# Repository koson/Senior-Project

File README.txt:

This is the repository for the "Granny Safe" senior project

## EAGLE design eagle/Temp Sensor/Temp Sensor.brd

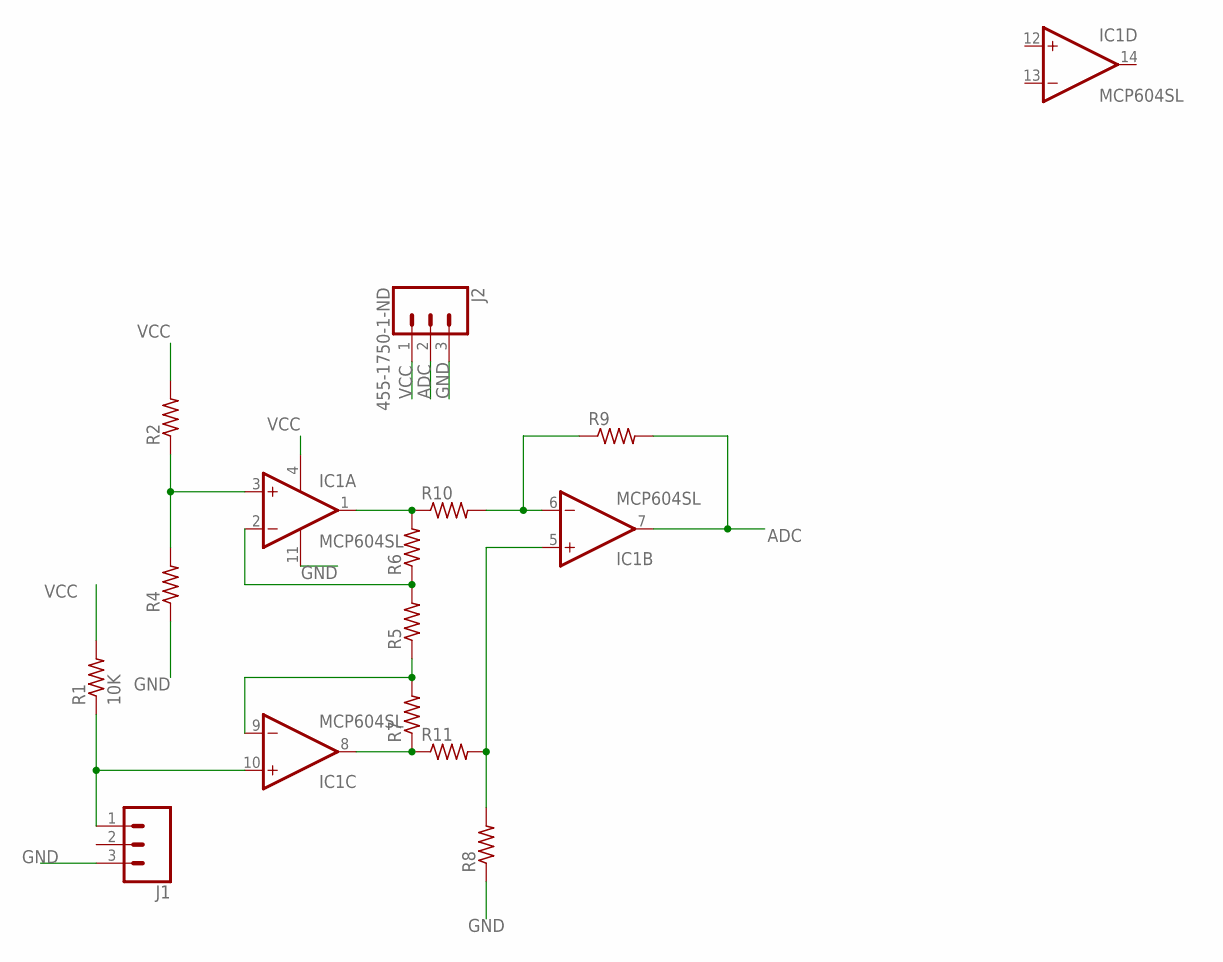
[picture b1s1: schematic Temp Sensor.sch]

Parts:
IC1: MCP604SL; SO14
J1: CONN_03SCREW_LOCK; SCREWTERMINAL-3.5MM-3_LOCK.007S
J2: 455-1750-1-ND; 1X03
R1: 10K; R0603
R2, R4, R5, R6, R7, R8, R9, R10, R11: R-US_R0603; R0603

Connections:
ADC: IC1.7 (OUT), J2.2, R9.2
GND: IC1.11 (V-), J1.3, J2.3, R4.1, R8.1
unnamed: IC1.10 (+IN), J1.1, R1.1
unnamed: IC1.3 (+IN), R2.1, R4.2
unnamed: IC1.8 (OUT), R7.1, R11.1
unnamed: IC1.1 (OUT), R6.2, R10.1
unnamed: IC1.2 (-IN), R5.2, R6.1
unnamed: IC1.9 (-IN), R5.1, R7.2
unnamed: IC1.5 (+IN), R8.2, R11.2
unnamed: IC1.6 (-IN), R9.1, R10.2
VCC: IC1.4 (V+), J2.1, R1.2, R2.2

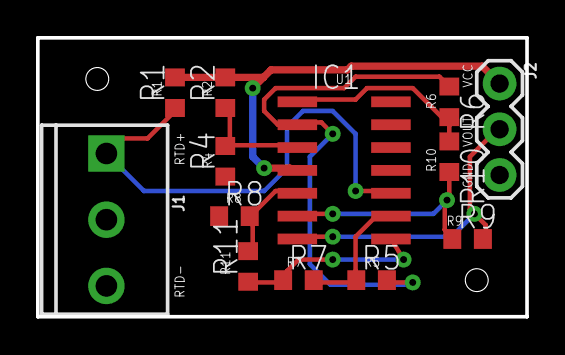
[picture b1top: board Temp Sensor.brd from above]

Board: 2 copper layers, 27.2 x 15.5 mm, 13 parts (0 on the bottom side), 11 nets.

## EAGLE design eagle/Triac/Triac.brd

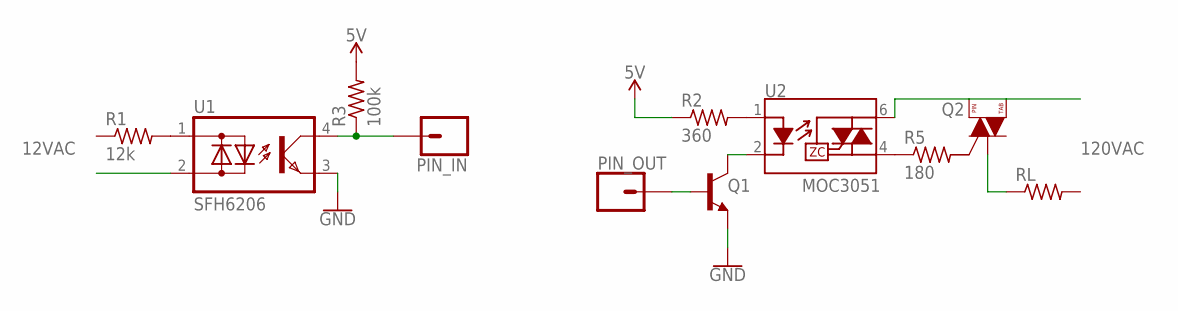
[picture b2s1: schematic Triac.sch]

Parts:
PIN_IN: CONN_01; 1X01
PIN_OUT: CONN_01; 1X01
Q1: TRANS_NPN-MMBTA42; SOT23-3
Q2: BT137-600E; SOT223
R1: 12k; R0603
R2: 360; R0603
R3: 100k; R0603
R5: 180; R0603
RL: R-US_R0603; R0603
U1: SFH6206; DIL4-SMD
U2: TRIAC_OPTOCOUPLER-MOC3063SM; DIP8SMD

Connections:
5V: R2.1, R3.2
GND: Q1.2 (E), U1.3 (E)
unnamed: R1.2, U1.1 (AC1)
unnamed: PIN_IN.1, R3.1, U1.4 (C)
unnamed: R2.2, U2.1 (A)
unnamed: R5.1, U2.4 (T2)
unnamed: Q2.2 (T2), Q2.4 (T2), U2.6 (T1)
unnamed: Q1.3 (C), U2.2 (K)
unnamed: PIN_OUT.1, Q1.1 (B)
unnamed: Q2.1 (T1), RL.1

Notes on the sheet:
MOC3051
12VAC
120VAC

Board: 2 copper layers, 11 parts (0 on the bottom side), 10 nets, no tracks yet.

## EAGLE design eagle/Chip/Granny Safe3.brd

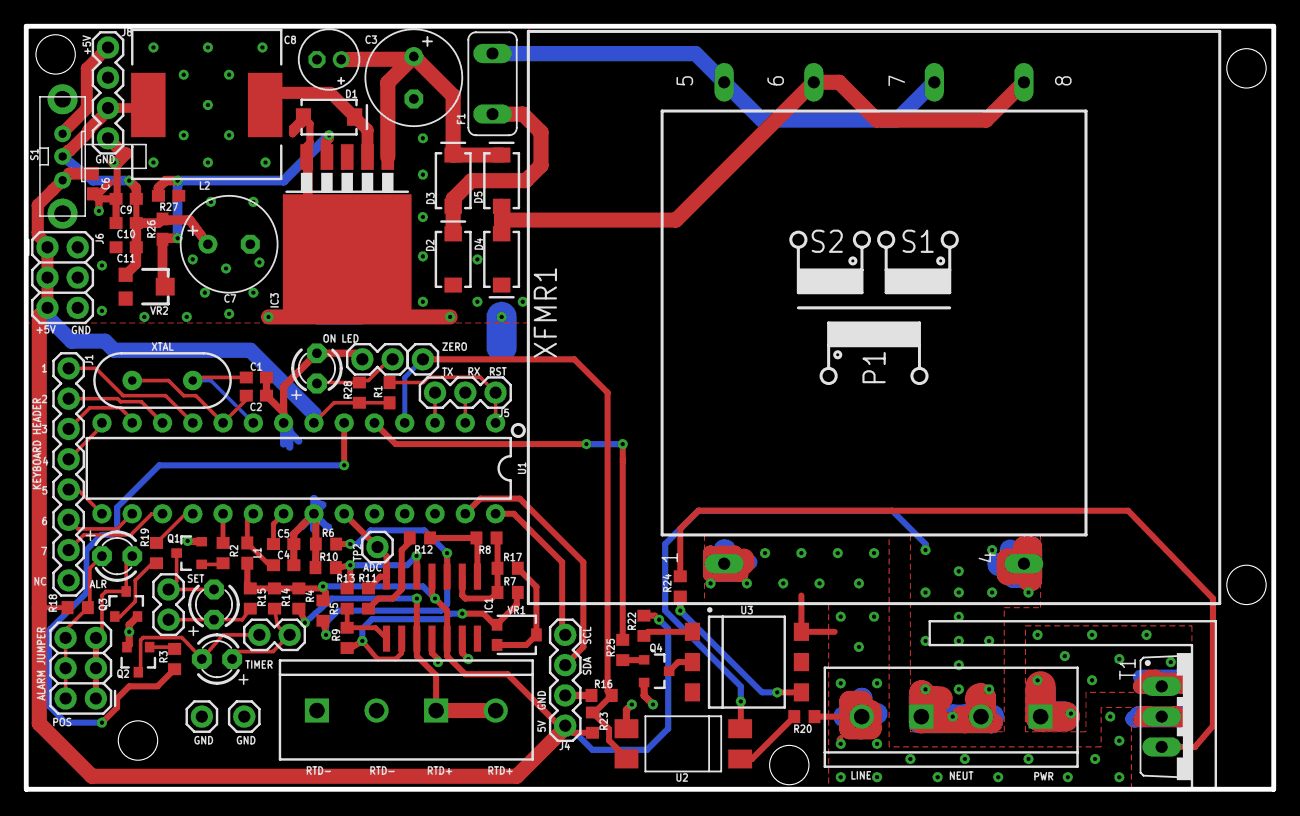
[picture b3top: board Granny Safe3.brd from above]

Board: 2 copper layers, 104.6 x 64.0 mm, 85 parts (0 on the bottom side), 60 nets.

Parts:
ALR_LED: LED3MM
C1, C2: 22pF; 0603
C3, C7: 470u; E3,5-8
C4, C5, C6, C9: 0.1uF; 0603
C8: 100u; E2-5
C10: 100pF; 0603
C11: 1nF; 0603
D1, D2, D3, D4, D5: SMA-DIODE
F1: 1.5A; TE5
H1, H2, H3, H4, H5: STAND-OFF
IC1: MCP604SL; SO14
IC3: TO263-5
J1: 3x4 Keypad; 1X08
J2, J6: FEMALE 2x3; 2X3
J3, J10: SCREW-4; SCREWTERMINAL-5MM-2
J4: i2c_16x2; 1X04
J5: 1X03
J7, J11, J12: 1X02
J8: RES JUMPER; 1X04
L1: 10uH; 0603
L2: INDUCTOR; CR75
ON_LED: LED3MM
Q1, Q2, Q3: SOT23-3
Q4: 2N3904; SOT23-3
R1: 10k; 0603
R2, R3, R19, R25: 2k; R0603
R4, R5: 2.4k; R0603
R6: 100; R0603
R7, R20, R23: 10k; R0603
R8, R9: 20k; R0603
R10, R11: 15k; R0603
R12, R13: 3k; R0603
R14, R15, R18, R28: 150; R0603
R16: 1M; R0603
R17: 5k; R0603
R22: 220; R0603
R24: 180; R0603
R26: 3.3k; 0603
R27: 1k; 0603
S1: EG1213
SET_LED: LED3MM
T1: BT137; TO220BV
TIM_LED: LED3MM
TP1, TP2, TP3, TP5: 1X01
U1: 328P; DIP28
U2: SFH6206; DIL4-SMD
U3: MOC3051; DIP8SMD
VR1: 10k; TRIMPOT-SMD-3MM-CLOSED
VR2: 10k; TRIMPOT-SMD-TC33X
XFMR1: EE20-2
XTAL: 16MHz; HC49US

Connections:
5V: C6.1, IC1.4, IC1.12, J4.1, J6.1, J6.3, J6.5, L1.1, R1.2, R4.2, R5.2, R14.2, R15.2, R18.2, R22.1, R23.2, R28.2, S1.1, U1.7
ADC0: IC1.7, R11.2, TP2.1, U1.23
ALR: R19.1, U1.18
GATE: R25.1, U1.5
GND: C1.1, C2.1, C3.-, C4.2, C5.2, C6.2, C7.-, C8.-, C9.2, C10.2, C11.2, D1.A, D2.A, D4.C, IC1.11, IC1.13, IC3.3, IC3.5, IC3.6, J3.1, J3.2, J4.2, J6.2, J6.4, J6.6, J8.4, J12.2, ON_LED.K, Q1.2, Q2.2, Q3.2, Q4.2, R6.1, R10.1, R16.1, R27.1, TP3.1, TP5.1, U1.8, U1.22, U2.3, VR2.3
LINE: J10.4, R20.1, T1.T2, U3.6, XFMR1.1
unnamed: C1.2, U1.9, XTAL.2
unnamed: C2.2, U1.10, XTAL.1
unnamed: J1.7, U1.17
unnamed: J8.1, S1.3
unnamed: C5.1, U1.21
unnamed: J1.6, U1.16
unnamed: J1.5, U1.15
unnamed: J1.4, U1.14
unnamed: J1.3, U1.13
unnamed: J1.2, U1.12
unnamed: J1.1, U1.11
unnamed: Q1.1, R2.2
unnamed: IC1.10, J3.3, J3.4, R4.1
unnamed: Q2.1, R3.2
unnamed: IC1.3, R5.1, R6.2
unnamed: IC1.1, R8.2, R12.1
unnamed: J7.1, R15.1, SET_LED.A
unnamed: J11.1, R14.1, TIM_LED.A
unnamed: J11.2, Q2.3, TIM_LED.K
unnamed: J7.2, Q1.3, SET_LED.K
unnamed: R17.2, VR1.2, VR1.3
unnamed: D2.C, D3.A, F1.2
unnamed: ALR_LED.K, J2.1, J2.3, J2.5, Q3.3
unnamed: IC1.2, R7.2, R8.1, R17.1
unnamed: IC1.8, R9.1, R13.1
unnamed: IC1.9, R7.1, R9.2, VR1.1
unnamed: IC1.5, R10.2, R13.2
unnamed: IC1.6, R11.1, R12.2
unnamed: R20.2, U2.1
unnamed: R24.2, T1.G
unnamed: R22.2, U3.1
unnamed: R24.1, U3.4
unnamed: IC3.4, R26.1, R27.2, VR2.2
unnamed: Q4.3, U3.2
unnamed: Q4.1, R25.2
unnamed: J12.1, ON_LED.A, R28.1
unnamed: F1.1, XFMR1.5, XFMR1.7
unnamed: C7.+, C9.1, C10.1, C11.1, J8.3, L2.P$2, R26.2, S1.2, VR2.1
unnamed: ALR_LED.A, J2.2, J2.4, J2.6, R18.1
unnamed: Q3.1, R19.2
unnamed: D4.A, D5.A, XFMR1.6, XFMR1.8
unnamed: C4.1, L1.2, U1.20
unnamed: D1.C, IC3.2, L2.P$1
unnamed: C3.+, C8.+, D3.C, D5.C, IC3.1
NEUT: J10.2, J10.3, U2.2, XFMR1.4
PWR: J10.1, T1.T1
RST: J5.1, R1.1, U1.1
RX: J5.2, U1.2
SCL: J4.4, U1.28
SDA: J4.3, U1.27
SET: R2.1, U1.19
TX: J5.3, U1.3
T_EN: R3.1, U1.6
ZERO: R16.2, R23.1, TP1.1, U1.4, U2.4

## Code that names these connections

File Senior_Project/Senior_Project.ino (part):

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
#define ALARM_PIN     12    //pin 18 on chip, used to control alarm speaker and led
#define SETPOINT_PIN  13    //pin 19 on chip, used control setpoint led
#define ZERO_SENSE    2     //pin 4 on chip, used as external interrupt pin to capture zero crossing event
#define GATE_PIN      3     //pin 5 on chip, used to control the triggering of the triac (pretty sure want PWM here, so chose PWM PIN)
#define HOT_LED_PIN   4     //probably need to change pin (6 on chip currently)
#define KP            40.0     // PID proportional factor
#define KI            1    // PID integral factor
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
  pinMode(ALARM_PIN, OUTPUT);         //controls alarm speaker and led bjt
  pinMode(SETPOINT_PIN, OUTPUT);      // enables setpoint entered led
  pinMode(ZERO_SENSE, INPUT);         // reads the zero sense signal
  pinMode(GATE_PIN, OUTPUT);          //controls triac gate pin
  pinMode(HOT_LED_PIN, OUTPUT);       //used to control led to signal >120F

  // set up Timer1 
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void zero_crossing() {
  if (zero_state) { //zero sense enabled and hotplate not in full off condition  
    TCCR1B=0x04;                  //start timer 1 with divide by 256 input
    TCNT1 = 0;                    //reset timer 1 - count from zero
  }   
}

ISR(TIMER1_COMPA_vect){                 //comparator match interrupt
  if (zero_state && OCR1A < windowsize) {                     //zero sense is enable
    digitalWrite(GATE_PIN, HIGH);       //set TRIAC gate to high
    TCNT1 = 65536 + (-(windowsize+2) + OCR1A);      //trigger pulse width, will be full half wave - delay
  }                                     //bigger than 500 and starts skipping some half waves
                                        //given the rise/fall of zero-cross, 500 ~ half wave
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
ISR(TIMER1_OVF_vect){                   //timer 1 overflow interrupt
  if (zero_state) {                     //zero sense is enable
    digitalWrite(GATE_PIN,LOW);         //turn off TRIAC gate
    TCCR1B = 0x00;                      //disable timer, stop unintended triggers
  }
}
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  }
  else {                    //if no setpoint keep hotplate off and disregard zero sense
    zero_state = false;           
    digitalWrite(GATE_PIN,LOW);
  }
}

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
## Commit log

2023-02-16 add kicad

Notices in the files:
parts and their libraries:
SparkFun-Capacitors: Licensing: Creative Commons ShareAlike 4.0 International - https://creativecommons.org/licenses/by-sa/4.0
